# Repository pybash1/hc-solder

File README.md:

# hc-solder
This is a mini touch sensor circuit using a simple NPN transistor. The circuit uses the human body's electrical resistance to complete the circuit, the small voltage from the body(when we touch the exposed pads) goes to the base of the transistor which then lets the current from the 9V battery pass onto the LED via the transistor.

By `@pybash` on Slack

# Schematic

# PCB

# 3D View

# Real circuit

# BOM
- 1 Battery holder
- 1 9V Battery
- 2 220ohm resistor
- 1 NPN transistor
- 1 Red LED
- 2 Mounting hold pads

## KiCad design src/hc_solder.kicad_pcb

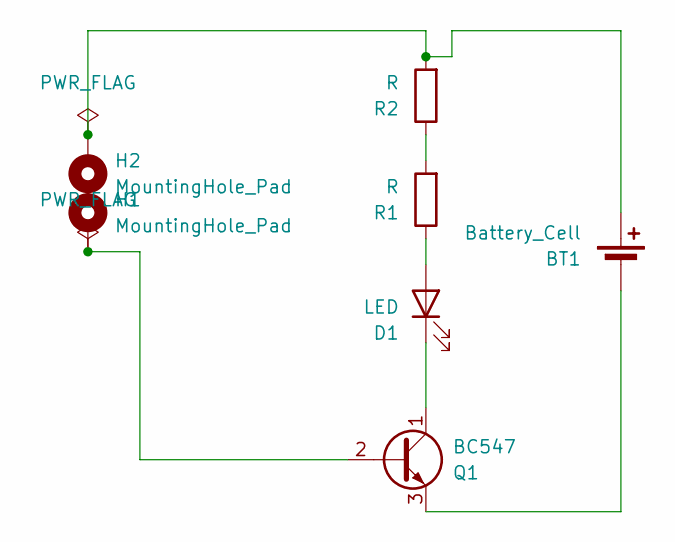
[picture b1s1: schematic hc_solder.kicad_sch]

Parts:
BT1: Battery_Cell; BatteryHolder_Keystone_3034_1x20mm
D1: LED; LED_D5.0mm
H1, H2: MountingHole_Pad; MountingHole_5.5mm_Pad
Q1: BC547; TO-92L_HandSolder
R1, R2: R; R_Axial_DIN0207_L6.3mm_D2.5mm_P7.62mm_Horizontal

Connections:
unnamed: BT1.1 (+), H2.1, R2.2
unnamed: BT1.2 (-), Q1.3 (E)
unnamed: D1.2 (A), R1.1
unnamed: D1.1 (K), Q1.1 (C)
unnamed: H1.1, Q1.2 (B)
unnamed: R1.2, R2.1

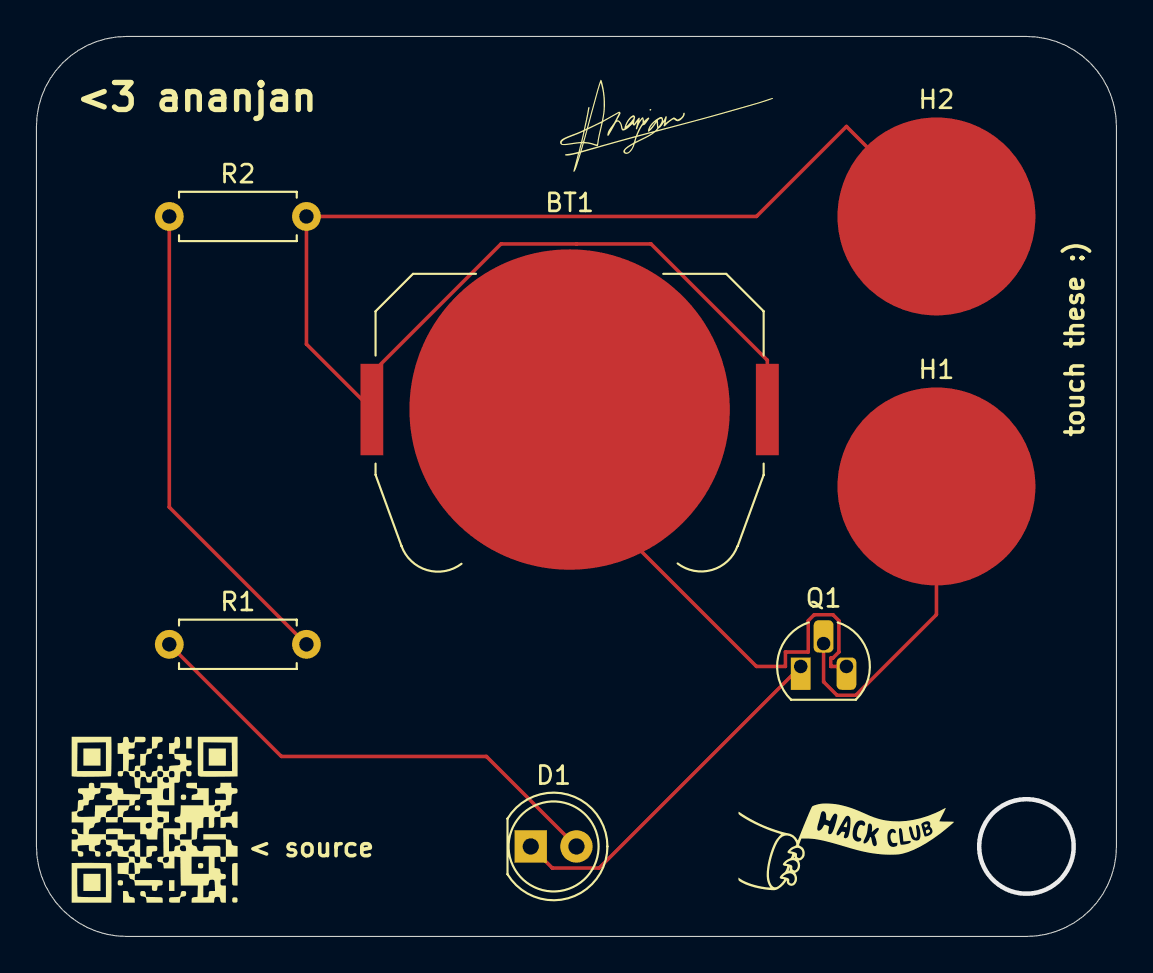
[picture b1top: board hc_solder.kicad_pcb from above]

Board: 2 copper layers, 60.0 x 50.0 mm, 7 parts (0 on the bottom side), 6 nets.

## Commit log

2025-05-03 Rename test.txt to src/test.txt
